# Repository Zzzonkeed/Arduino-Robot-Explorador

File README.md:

# Arduino-Robot-Explorador
Robot explorador autónomo utilizando Arduino

El robot cuenta con un chasis extraído de un auto RC 4x4, la idea es que el manejo de los motores se encuentre aislado
de la lógica, es por ello que se utilizara un microcontrolador dedicado exclusivamente a ello, conectado mediante I2c al 
microcontrolador Master.

El proyecto se divide en esas dos etapas (por ahora), el control de motores y la placa master que leerá los sensores y 
enviara por medio de I2C los comando al controlador de motores, ambas placas utilizaran un microcontrolador
Atmega328P con el Bootloader de Arduino UNO.

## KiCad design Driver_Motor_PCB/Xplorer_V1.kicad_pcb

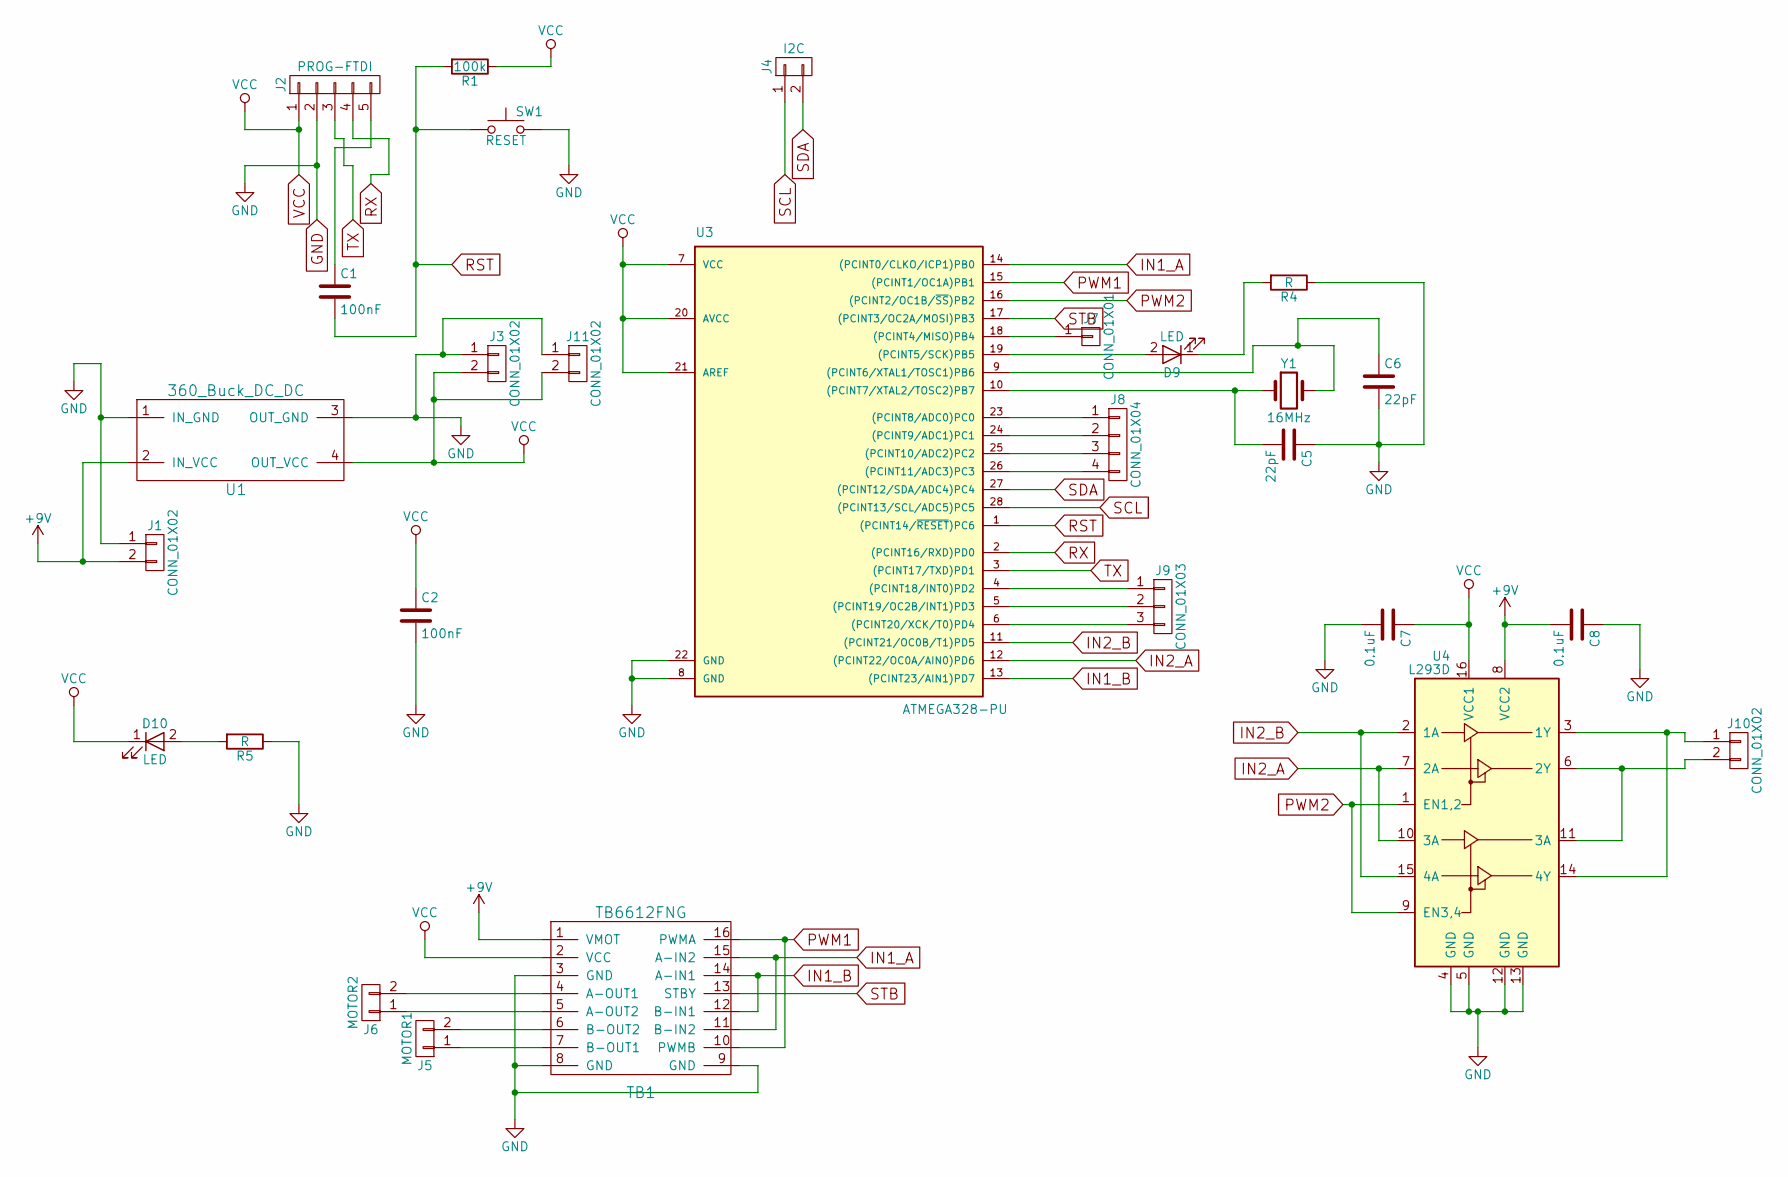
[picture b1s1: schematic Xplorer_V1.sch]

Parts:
C1, C2: 100nF; C_Disc_D3.0mm_W1.6mm_P2.50mm
C5, C6: 22pF; C_Disc_D3.0mm_W1.6mm_P2.50mm
C7, C8: 0.1uF; C_Disc_D3.0mm_W1.6mm_P2.50mm
D9, D10: LED; LED_D5.0mm_FlatTop
J1, J3, J10, J11: CONN_01X02; Pin_Header_Angled_1x02_Pitch2.54mm
J2: PROG-FTDI; Pin_Header_Angled_1x05_Pitch2.54mm
J4: I2C; Pin_Header_Angled_1x02_Pitch2.54mm
J5: MOTOR1; Pin_Header_Angled_1x02_Pitch2.54mm
J6: MOTOR2; Pin_Header_Angled_1x02_Pitch2.54mm
J7: CONN_01X01; Pin_Header_Straight_1x01_Pitch2.54mm
J8: CONN_01X04; Pin_Header_Angled_1x04_Pitch2.54mm
J9: CONN_01X03; Pin_Header_Angled_1x03_Pitch2.54mm
R1: 100k; R_Axial_DIN0204_L3.6mm_D1.6mm_P7.62mm_Horizontal
R4, R5: R; R_Axial_DIN0204_L3.6mm_D1.6mm_P7.62mm_Horizontal
SW1: RESET; SW_PUSH_SMALL
TB1: TB6612FNG
U1: 360_Buck_DC_DC
U3: ATMEGA328-PU; DIP-28_W7.62mm_LongPads
U4: L293D; DIP-16_W7.62mm
Y1: 16MHz; Crystal_HC18-U_Vertical

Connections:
+9V: C8.2, J1.2, TB1.1 (VMOT), U1.2 (IN_VCC), U4.8 (VCC2)
GND: C2.2, C5.1, C6.2, C7.2, C8.1, J1.1, J2.2, J3.1, J11.1, R4.1, R5.1, SW1.2, TB1.3 (GND), TB1.8 (GND), TB1.9 (GND), U1.1 (IN_GND), U1.3 (OUT_GND), U3.8 (GND), U3.22 (GND), U4.4 (GND), U4.5 (GND), U4.12 (GND), U4.13 (GND)
IN1_A: TB1.11 (B-IN2), TB1.15 (A-IN2), U3.14 ((PCINT0/CLKO/ICP1)PB0)
IN1_B: TB1.12 (B-IN1), TB1.14 (A-IN1), U3.13 ((PCINT23/AIN1)PD7)
IN2_A: U3.12 ((PCINT22/OC0A/AIN0)PD6), U4.7 (2A), U4.10 (3A)
IN2_B: U3.11 ((PCINT21/OC0B/T1)PD5), U4.2 (1A), U4.15 (4A)
unnamed: C1.1, J2.5
unnamed: C5.2, U3.10 ((PCINT7/XTAL2/TOSC2)PB7), Y1.1
unnamed: C6.1, U3.9 ((PCINT6/XTAL1/TOSC1)PB6), Y1.2
unnamed: D9.1 (K), R4.2
unnamed: D9.2 (A), U3.19 ((PCINT5/SCK)PB5)
unnamed: D10.2 (A), R5.2
unnamed: J5.1, TB1.7 (B-OUT1)
unnamed: J5.2, TB1.6 (B-OUT2)
unnamed: J6.1, TB1.5 (A-OUT2)
unnamed: J6.2, TB1.4 (A-OUT1)
unnamed: J7.1, U3.18 ((PCINT4/MISO)PB4)
unnamed: J8.1, U3.23 ((PCINT8/ADC0)PC0)
unnamed: J8.2, U3.24 ((PCINT9/ADC1)PC1)
unnamed: J8.3, U3.25 ((PCINT10/ADC2)PC2)
unnamed: J8.4, U3.26 ((PCINT11/ADC3)PC3)
unnamed: J9.1, U3.4 ((PCINT18/INT0)PD2)
unnamed: J9.2, U3.5 ((PCINT19/OC2B/INT1)PD3)
unnamed: J9.3, U3.6 ((PCINT20/XCK/T0)PD4)
unnamed: J10.1, U4.3 (1Y), U4.14 (4Y)
unnamed: J10.2, U4.6 (2Y), U4.11 (3A)
PWM1: TB1.10 (PWMB), TB1.16 (PWMA), U3.15 ((PCINT1/OC1A)PB1)
PWM2: U3.16 ((PCINT2/OC1B/~SS~)PB2), U4.1 (EN1,2), U4.9 (EN3,4)
RST: C1.2, R1.2, SW1.1, U3.1 ((PCINT14/~RESET~)PC6)
RX: J2.4, U3.2 ((PCINT16/RXD)PD0)
SCL: J4.1, U3.28 ((PCINT13/SCL/ADC5)PC5)
SDA: J4.2, U3.27 ((PCINT12/SDA/ADC4)PC4)
STB: TB1.13 (STBY), U3.17 ((PCINT3/OC2A/MOSI)PB3)
TX: J2.3, U3.3 ((PCINT17/TXD)PD1)
VCC: C2.1, C7.1, D10.1 (K), J2.1, J3.2, J11.2, R1.1, TB1.2 (VCC), U1.4 (OUT_VCC), U3.7 (VCC), U3.20 (AVCC), U3.21 (AREF), U4.16 (VCC1)

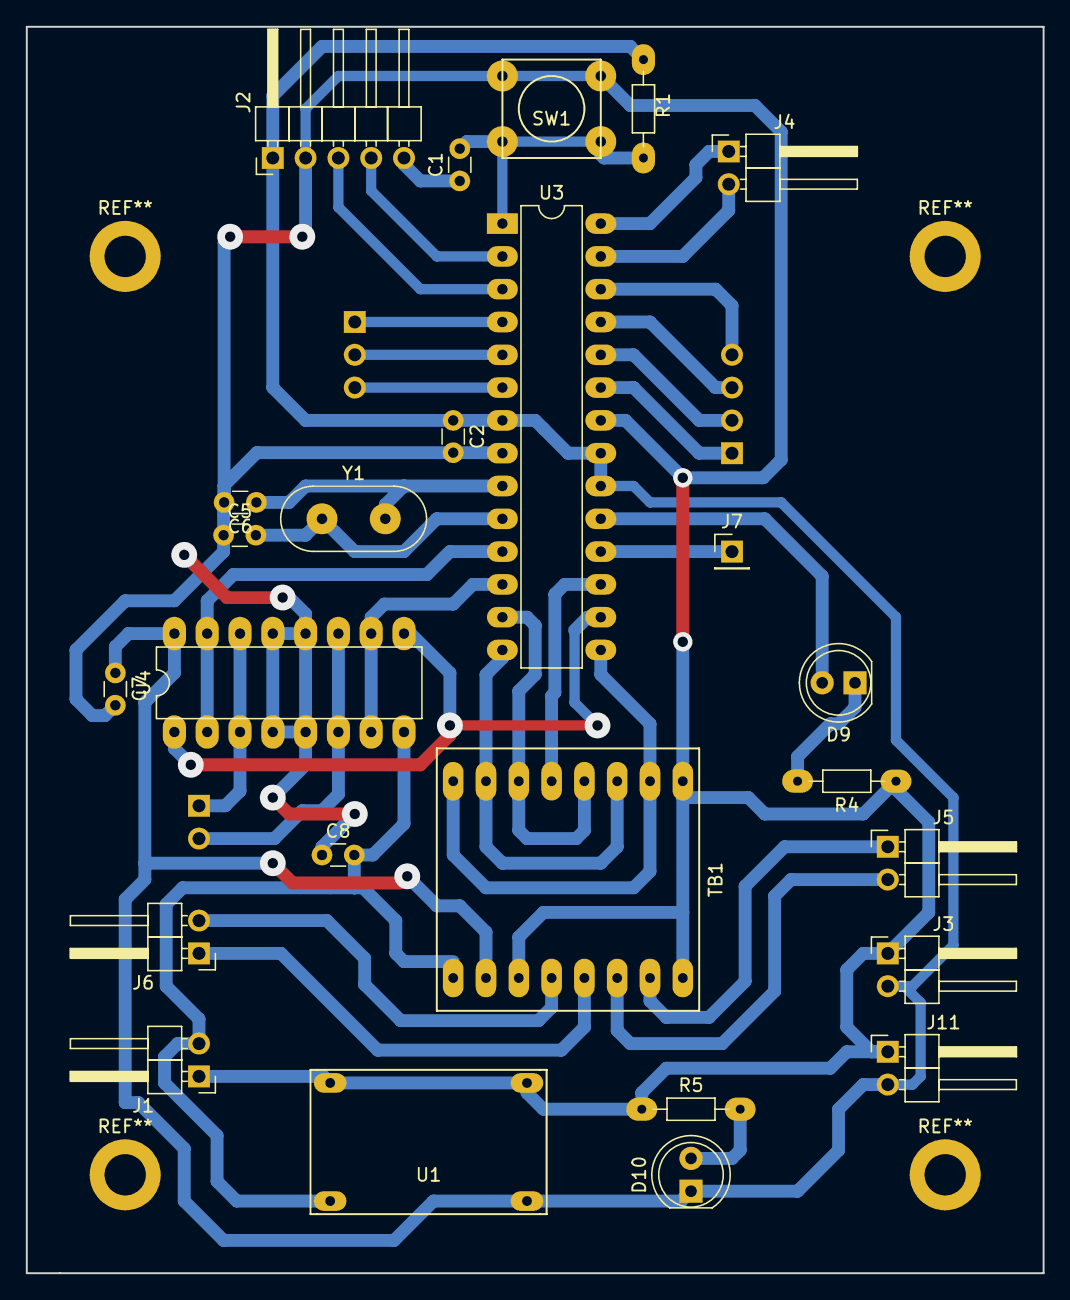
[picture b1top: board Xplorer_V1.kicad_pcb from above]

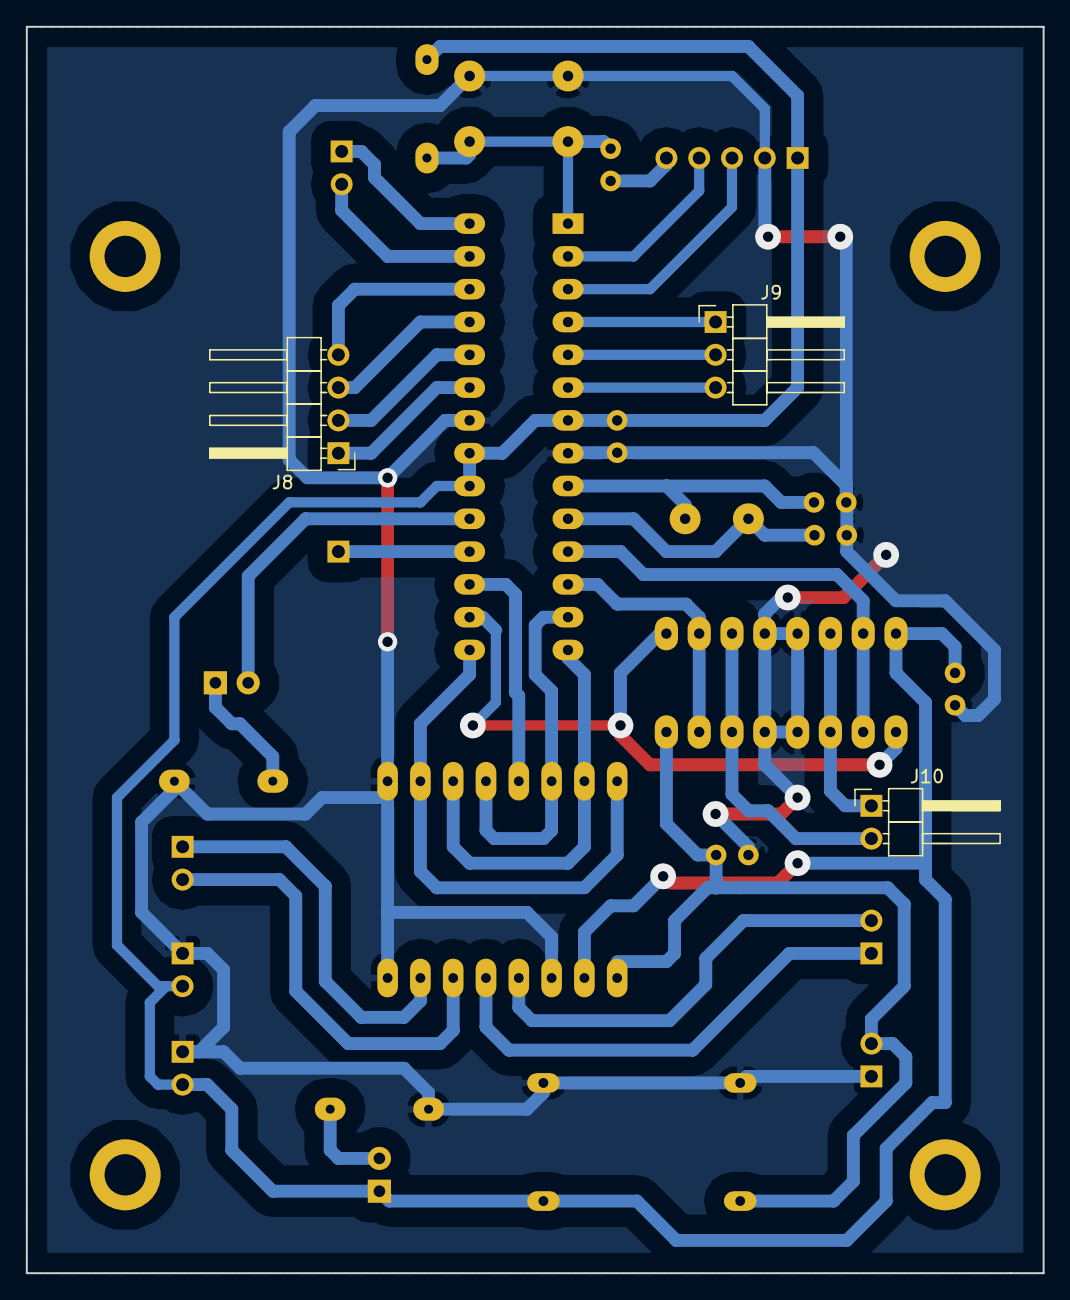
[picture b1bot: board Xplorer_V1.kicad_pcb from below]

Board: 2 copper layers, 78.7 x 96.5 mm, 28 parts (3 on the bottom side), 35 nets.

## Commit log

2018-01-03 Breve descripción del proyecto
2018-01-03 Rename Readme to README.md
2018-01-03 INFO
2018-01-03 Set theme jekyll-theme-hacker
